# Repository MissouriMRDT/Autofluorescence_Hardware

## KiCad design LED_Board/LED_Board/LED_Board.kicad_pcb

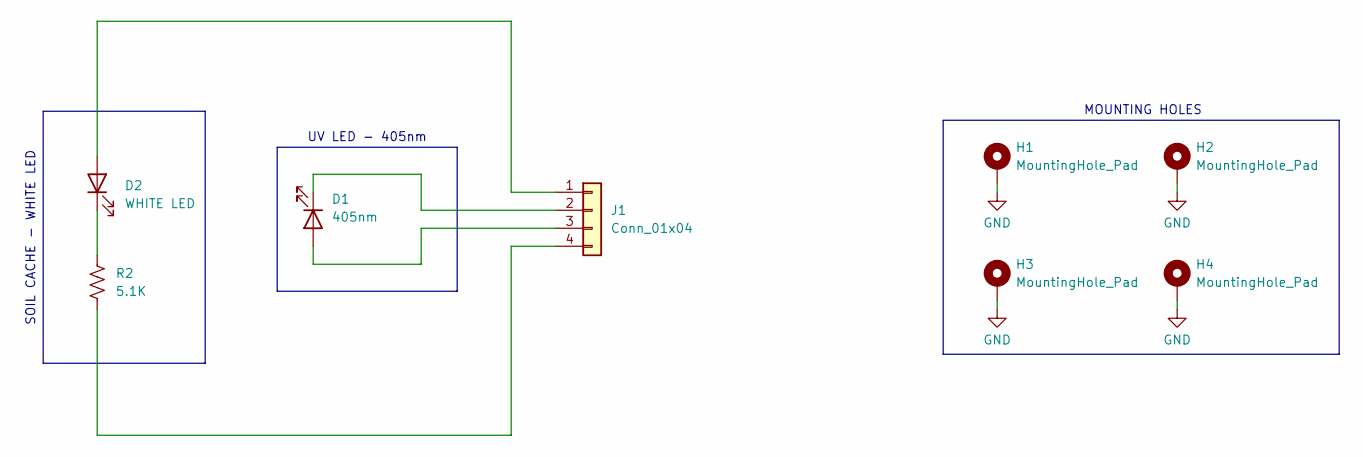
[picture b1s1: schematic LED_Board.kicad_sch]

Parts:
D1: 405nm; CUN06B1B
D2: WHITE LED; D_0603_1608Metric_Pad1.05x0.95mm_HandSolder
H1, H2, H3, H4: MountingHole_Pad; 4_40_Hole_Pad_Via
J1: Conn_01x04; JST_PH_B4B-PH-K_1x04_P2.00mm_Vertical
R2: 5.1K; R_0603_1608Metric_Pad0.98x0.95mm_HandSolder

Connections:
GND: H1.1 (1_1), H2.1 (1_1), H3.1 (1_1), H4.1 (1_1)
unnamed: D2.2 (A), J1.1
unnamed: D2.1 (K), R2.1
unnamed: D1.1, J1.2
unnamed: D1.2, J1.3
unnamed: J1.4, R2.2

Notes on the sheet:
UV LED - 405nm
MOUNTING HOLES
SOIL CACHE - WHITE LED

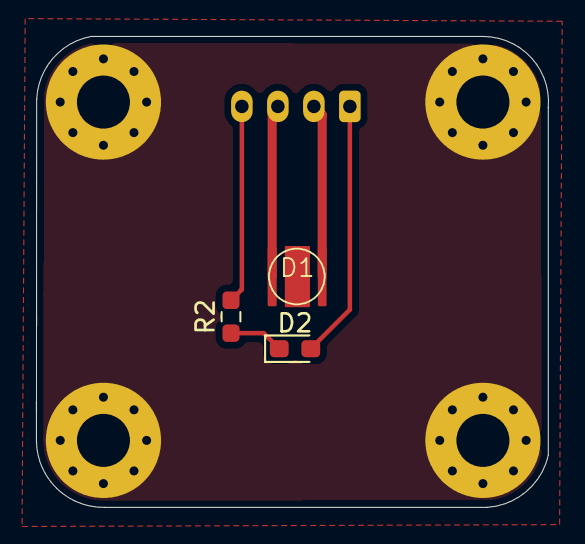
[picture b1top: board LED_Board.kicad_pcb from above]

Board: 2 copper layers, 28.4 x 26.2 mm, 8 parts (1 on the bottom side), 6 nets.

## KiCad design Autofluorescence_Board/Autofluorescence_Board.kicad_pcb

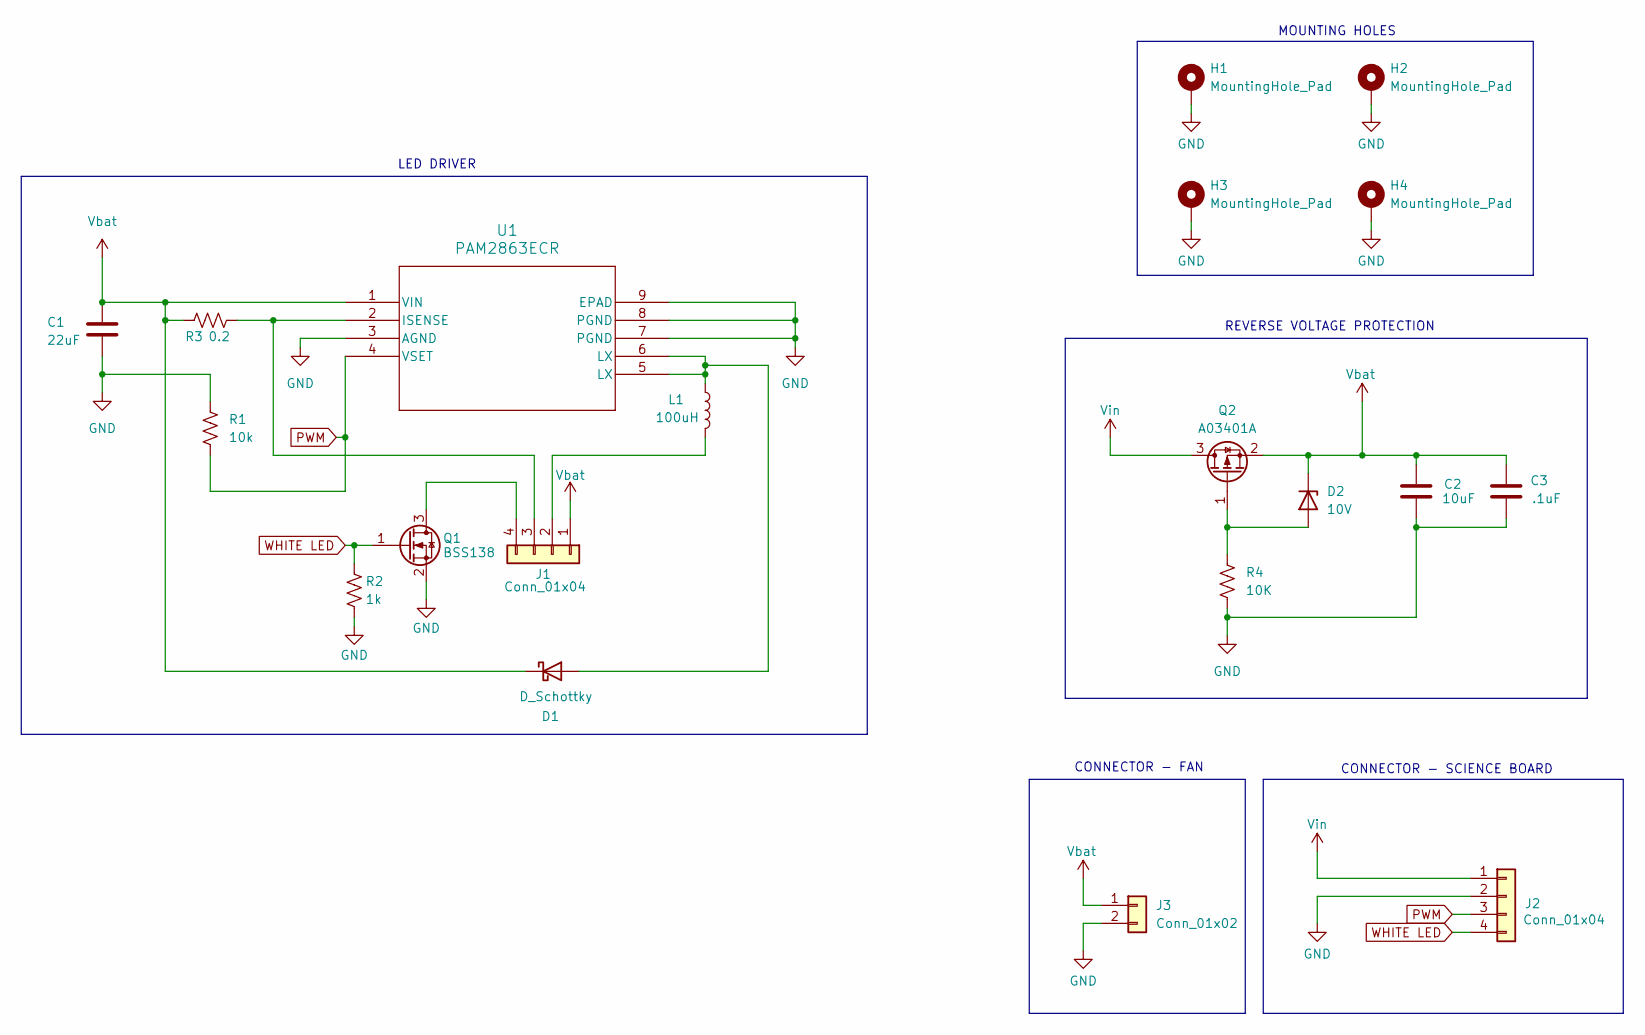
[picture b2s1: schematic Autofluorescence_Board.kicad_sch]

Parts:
C1: 22uF; C_1206_3216Metric_Pad1.33x1.80mm_HandSolder
C2: 10uF; C_0603_1608Metric_Pad1.08x0.95mm_HandSolder
C3: .1uF; C_0603_1608Metric_Pad1.08x0.95mm_HandSolder
D1: D_Schottky; D_SOD-123F
D2: 10V; SOD-123_ONS-L
H1, H2, H3, H4: MountingHole_Pad; 4_40_Hole_Pad_Via
J1, J2: Conn_01x04; JST_PH_S4B-PH-K_1x04_P2.00mm_Horizontal
J3: Conn_01x02; JST_PH_S2B-PH-K_1x02_P2.00mm_Horizontal
L1: 100uH; DR73
Q1: BSS138; SOT-23
Q2: A03401A; SOT-23
R1: 10k; R_0603_1608Metric_Pad0.98x0.95mm_HandSolder
R2: 1k; R_0603_1608Metric_Pad0.98x0.95mm_HandSolder
R3: 0.2; R_0805_2012Metric_Pad1.20x1.40mm_HandSolder
R4: 10K; R_0603_1608Metric_Pad0.98x0.95mm_HandSolder
U1: PAM2863ECR; Diodes_SO-8EP

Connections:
GND: C1.2, C2.2, C3.2, H1.1 (1_1), H2.1 (1_1), H3.1 (1_1), H4.1 (1_1), J2.2, J3.2, Q1.2 (S), R1.2, R2.2, R4.2, U1.3 (AGND), U1.7 (PGND), U1.8 (PGND), U1.9 (EPAD)
unnamed: D1.2 (A), L1.1, U1.5 (LX), U1.6 (LX)
unnamed: D2.2 (A), Q2.1 (G), R4.1
unnamed: J1.2, L1.2
unnamed: J1.3, R3.2, U1.2 (ISENSE)
unnamed: J1.4, Q1.3 (D)
PWM: J2.3, R1.1, U1.4 (VSET)
Vbat: C1.1, C2.1, C3.1, D1.1 (K), D2.1 (K), J1.1, J3.1, Q2.2 (S), R3.1, U1.1 (VIN)
Vin: J2.1, Q2.3 (D)
WHITE LED: J2.4, Q1.1 (G), R2.1

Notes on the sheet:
LED DRIVER
REVERSE VOLTAGE PROTECTION
MOUNTING HOLES
CONNECTOR - SCIENCE BOARD
CONNECTOR - FAN

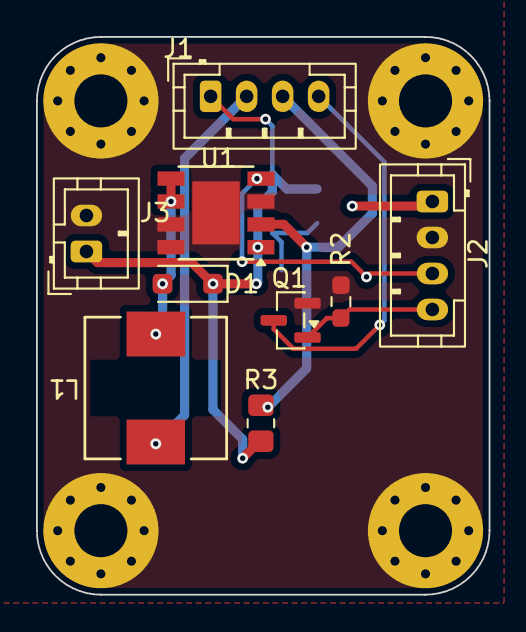
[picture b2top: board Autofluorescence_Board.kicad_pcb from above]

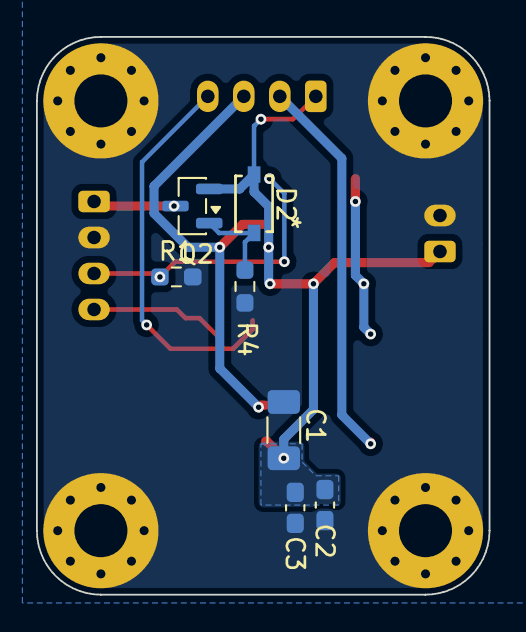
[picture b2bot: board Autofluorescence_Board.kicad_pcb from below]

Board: 2 copper layers, 25.1 x 31.0 mm, 20 parts (7 on the bottom side), 10 nets.

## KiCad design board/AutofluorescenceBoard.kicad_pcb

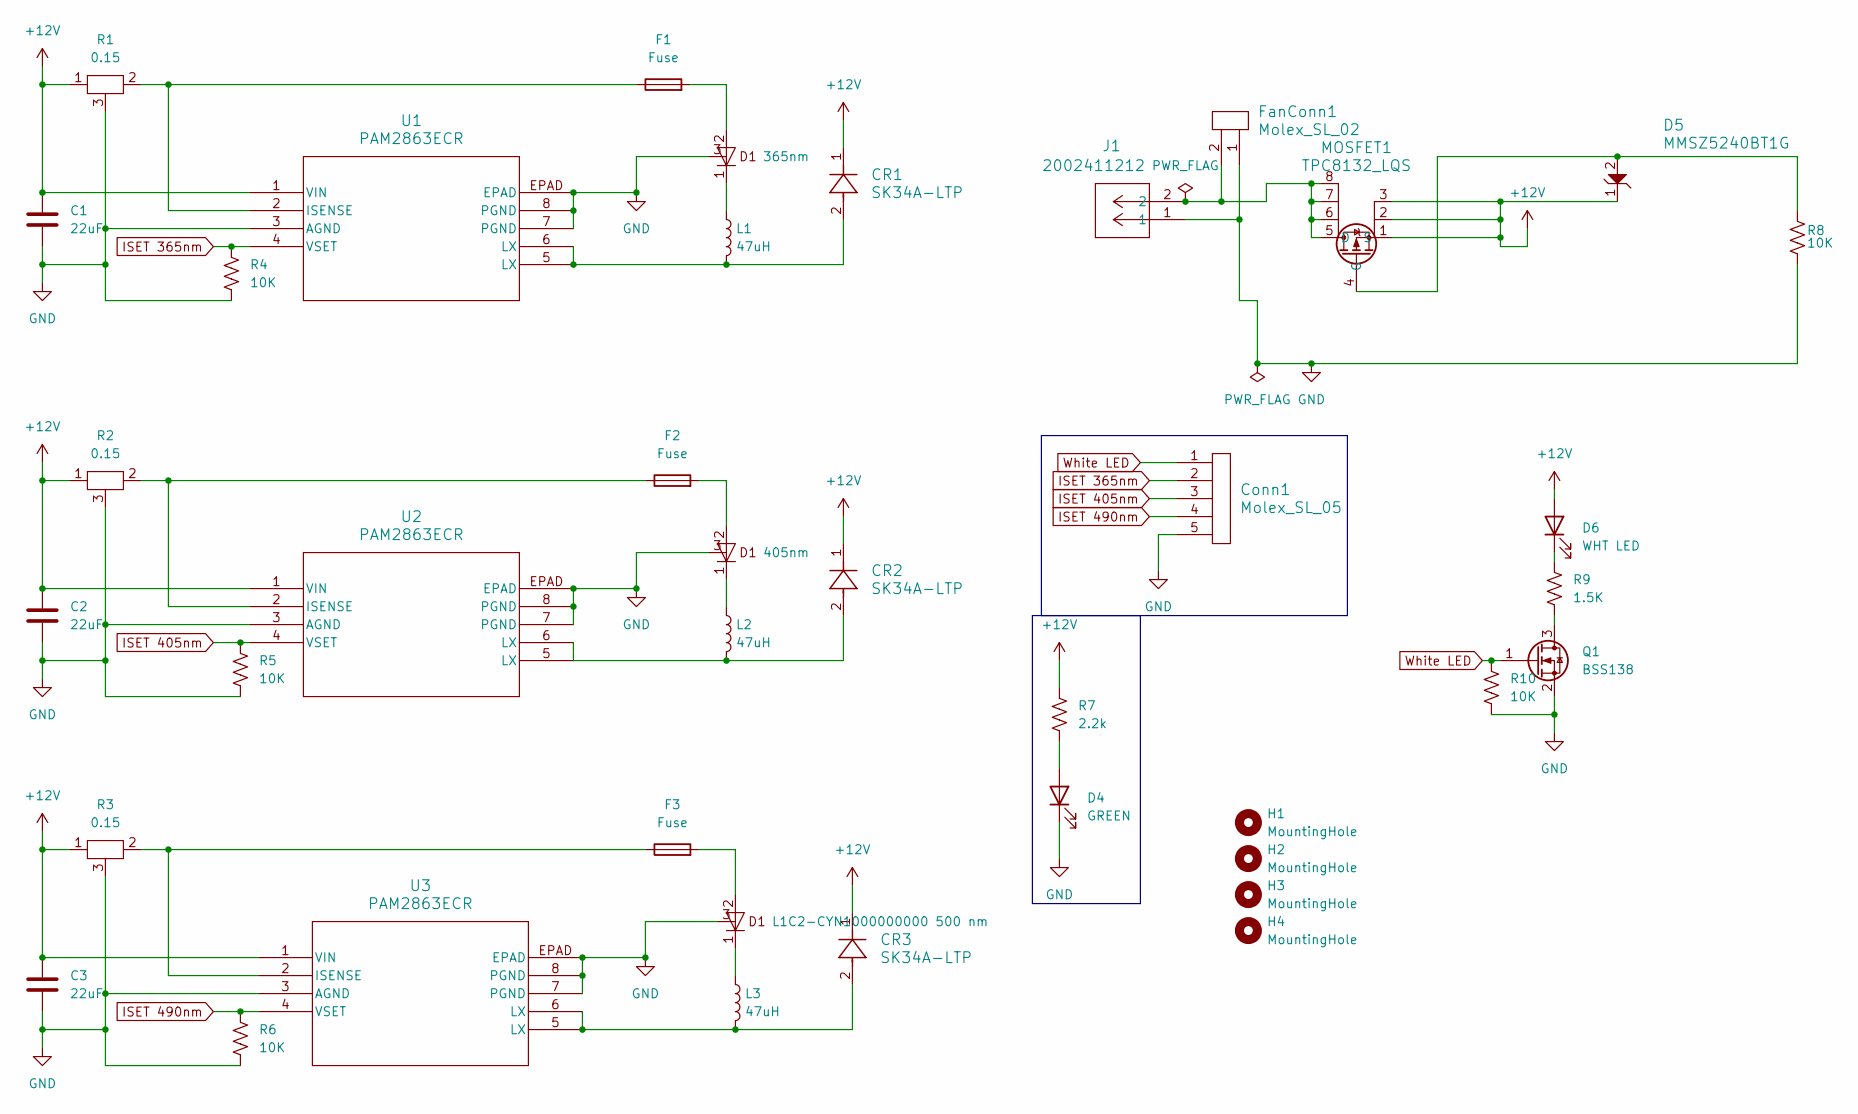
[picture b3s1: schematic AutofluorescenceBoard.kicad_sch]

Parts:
C1, C2, C3: 22uF; C_0805_2012Metric_Pad1.18x1.45mm_HandSolder
CR1, CR2, CR3: SK34A-LTP; SMADO-214AC_MCC
Conn1: Molex_SL_05; MOLEX_SL_05_Horizontal
D1: 365nm
D2: 405nm
D3: L1C2-CYN1000000000 500 nm; 490nm
D4: GREEN; LED_0603_1608Metric_Pad1.05x0.95mm_HandSolder
D5: MMSZ5240BT1G; SOD-123_ONS-L
D6: WHT LED; INS63AT5UW
F1, F2, F3: Fuse; Fuse_0603_1608Metric
FanConn1: Molex_SL_02; MOLEX_SL_02_Horizontal
H1, H2, H3, H4: MountingHole; M2_Hole
J1: 2002411212; MOLEX_SL_02_Horizontal
L1, L2, L3: 47uH; SRN6045TA-470M
MOSFET1: TPC8132_LQS; SOIC-8_3.9x4.9mm_P1.27mm
Q1: BSS138; SOT-23
R1, R2, R3: 0.15; TO508P1229X317-3N
R4, R5, R6, R8, R10: 10K; R_0603_1608Metric_Pad0.98x0.95mm_HandSolder
R7: 2.2k; R_0603_1608Metric_Pad0.98x0.95mm_HandSolder
R9: 1.5K; RES_R0603_ROM-M
U1, U2, U3: PAM2863ECR; SOIC_863ECR_DIO

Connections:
+12V: C1.1, C2.1, C3.1, CR1.1, CR2.1, CR3.1, D5.1, D6.2 (A), MOSFET1.1 (S), MOSFET1.2, MOSFET1.3, R1.1, R2.1, R3.1, R7.1, U1.1 (VIN), U2.1 (VIN), U3.1 (VIN)
GND: C1.2, C2.2, C3.2, Conn1.5, D1.3, D2.3, D3.3, D4.1 (K), FanConn1.1, H1.1, H2.1, H3.1, H4.1, J1.1, Q1.2 (S), R1.3, R2.3, R3.3, R4.2, R5.2, R6.2, R8.1, R10.2, U1.3 (AGND), U1.7 (PGND), U1.8 (PGND), U1.EPAD, U2.3 (AGND), U2.7 (PGND), U2.8 (PGND), U2.EPAD, U3.3 (AGND), U3.7 (PGND), U3.8 (PGND), U3.EPAD
ISET 365nm: Conn1.2, R4.1, U1.4 (VSET)
ISET 405nm: Conn1.3, R5.1, U2.4 (VSET)
ISET 490nm: Conn1.4, R6.1, U3.4 (VSET)
unnamed: CR1.2, L1.2, U1.5 (LX), U1.6 (LX)
unnamed: CR2.2, L2.2, U2.5 (LX), U2.6 (LX)
unnamed: CR3.2, L3.2, U3.5 (LX), U3.6 (LX)
unnamed: D1.1, L1.1
unnamed: D1.2, F1.2
unnamed: D2.1, L2.1
unnamed: D2.2, F2.2
unnamed: D3.1, L3.1
unnamed: D3.2, F3.2
unnamed: D4.2 (A), R7.2
unnamed: D6.1 (K), R9.1
unnamed: FanConn1.2, J1.2, MOSFET1.5 (D), MOSFET1.6, MOSFET1.7, MOSFET1.8
unnamed: D5.2, MOSFET1.4 (G), R8.2
unnamed: Q1.3 (D), R9.2
unnamed: F1.1, R1.2, U1.2 (ISENSE)
unnamed: F2.1, R2.2, U2.2 (ISENSE)
unnamed: F3.1, R3.2, U3.2 (ISENSE)
White LED: Conn1.1, Q1.1 (G), R10.1

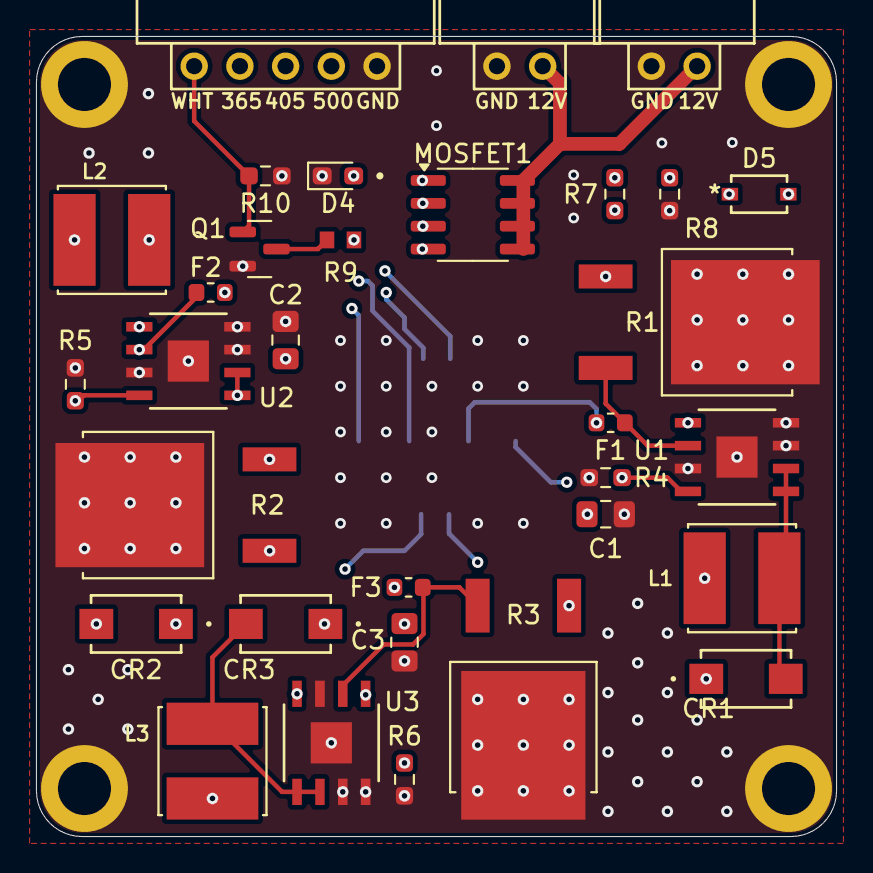
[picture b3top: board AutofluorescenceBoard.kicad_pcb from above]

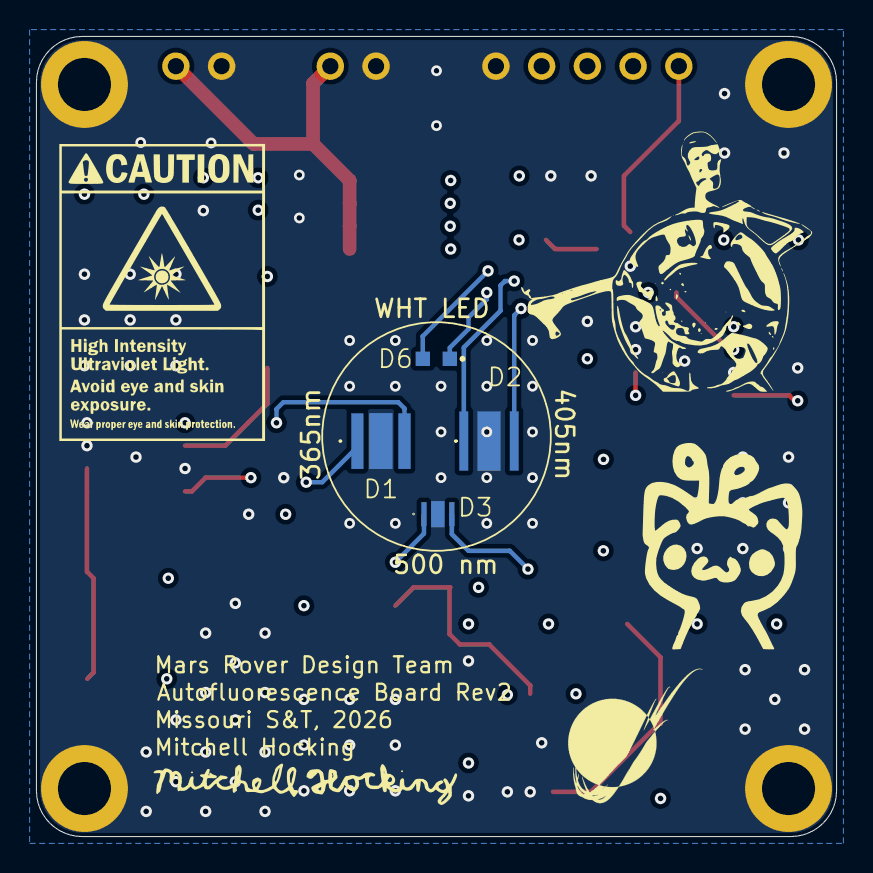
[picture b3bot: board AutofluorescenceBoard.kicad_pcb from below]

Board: 4 copper layers, 44.4 x 44.5 mm, 40 parts (4 on the bottom side), 23 nets.

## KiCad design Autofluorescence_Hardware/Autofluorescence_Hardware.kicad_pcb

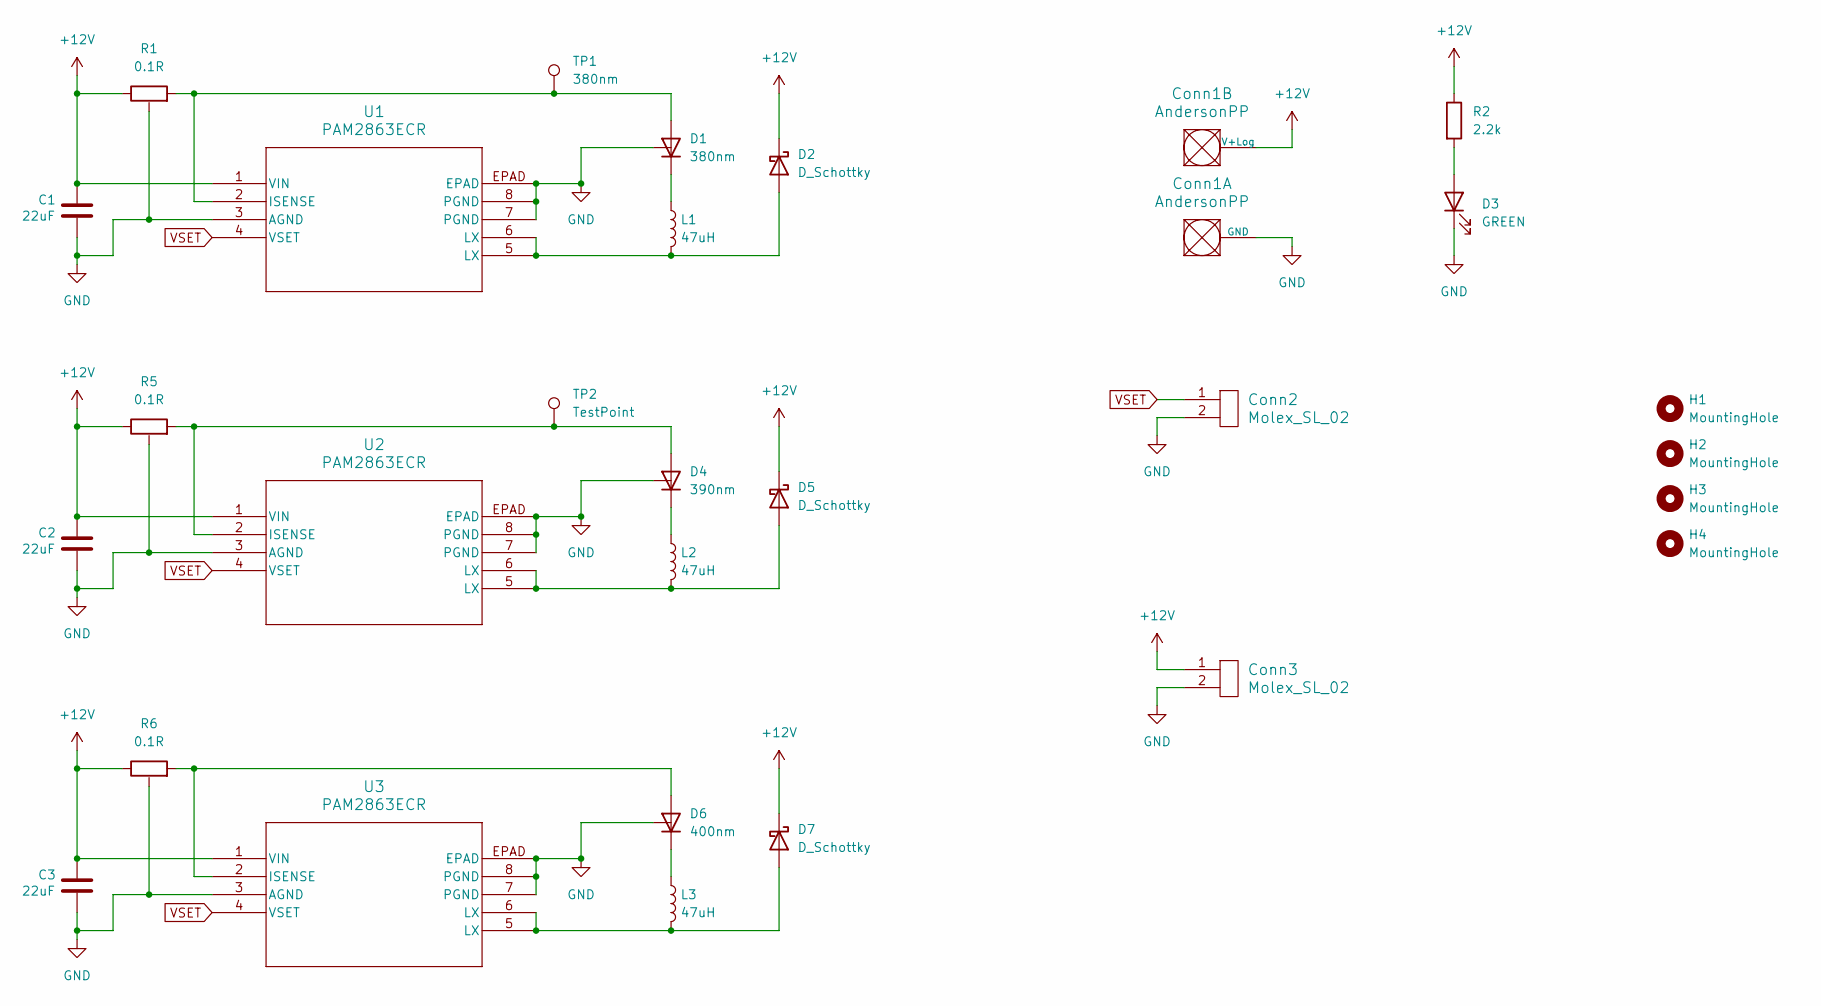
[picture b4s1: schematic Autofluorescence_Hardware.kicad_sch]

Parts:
C1, C2, C3: 22uF; C_0805_2012Metric_Pad1.18x1.45mm_HandSolder
Conn1: AndersonPP; Square_Anderson_2_H_Side_By_Side
Conn2, Conn3: Molex_SL_02; MOLEX_SL_02_Horizontal
D1: 380nm; SBT-10X-UV-A120-AHXXX-22
D2, D5, D7: D_Schottky; SK34A-LTP
D3: GREEN; LED_0603_1608Metric_Pad1.05x0.95mm_HandSolder
D4: 390nm; SBT-10X-UV-A120-AHXXX-22
D6: 400nm; SBT-10X-UV-A120-AHXXX-22
H1, H2, H3, H4: MountingHole; MountingHole_3.5mm
L1, L2, L3: 47uH; SRN6045TA-470M
R1, R5, R6: 0.1R; PWR163S-25-R100FE
R2: 2.2k; R_0603_1608Metric_Pad0.98x0.95mm_HandSolder
TP1: 380nm; TestPoint_Pad_D1.5mm
TP2: TestPoint; TestPoint_Pad_D1.5mm
U1, U2, U3: PAM2863ECR; SOIC_863ECR_DIO

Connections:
+12V: C1.1, C2.1, C3.1, Conn1.2 (V+Log), Conn3.1, D2.1 (K), D5.1 (K), D7.1 (K), R1.1, R2.1, R5.1, R6.1, U1.1 (VIN), U2.1 (VIN), U3.1 (VIN)
GND: C1.2, C2.2, C3.2, Conn1.1 (GND), Conn2.2, Conn3.2, D1.3, D3.1 (K), D4.3, D6.3, R1.3, R5.3, R6.3, U1.3 (AGND), U1.7 (PGND), U1.8 (PGND), U1.EPAD, U2.3 (AGND), U2.7 (PGND), U2.8 (PGND), U2.EPAD, U3.3 (AGND), U3.7 (PGND), U3.8 (PGND), U3.EPAD
unnamed: D1.2 (A), R1.2, TP1.1, U1.2 (ISENSE)
unnamed: D1.1 (K), L1.1
unnamed: D2.2 (A), L1.2, U1.5 (LX), U1.6 (LX)
unnamed: D3.2 (A), R2.2
unnamed: D4.2 (A), R5.2, TP2.1, U2.2 (ISENSE)
unnamed: D4.1 (K), L2.1
unnamed: D5.2 (A), L2.2, U2.5 (LX), U2.6 (LX)
unnamed: D6.2 (A), R6.2, U3.2 (ISENSE)
unnamed: D6.1 (K), L3.1
unnamed: D7.2 (A), L3.2, U3.5 (LX), U3.6 (LX)
VSET: Conn2.1, U1.4 (VSET), U2.4 (VSET), U3.4 (VSET)

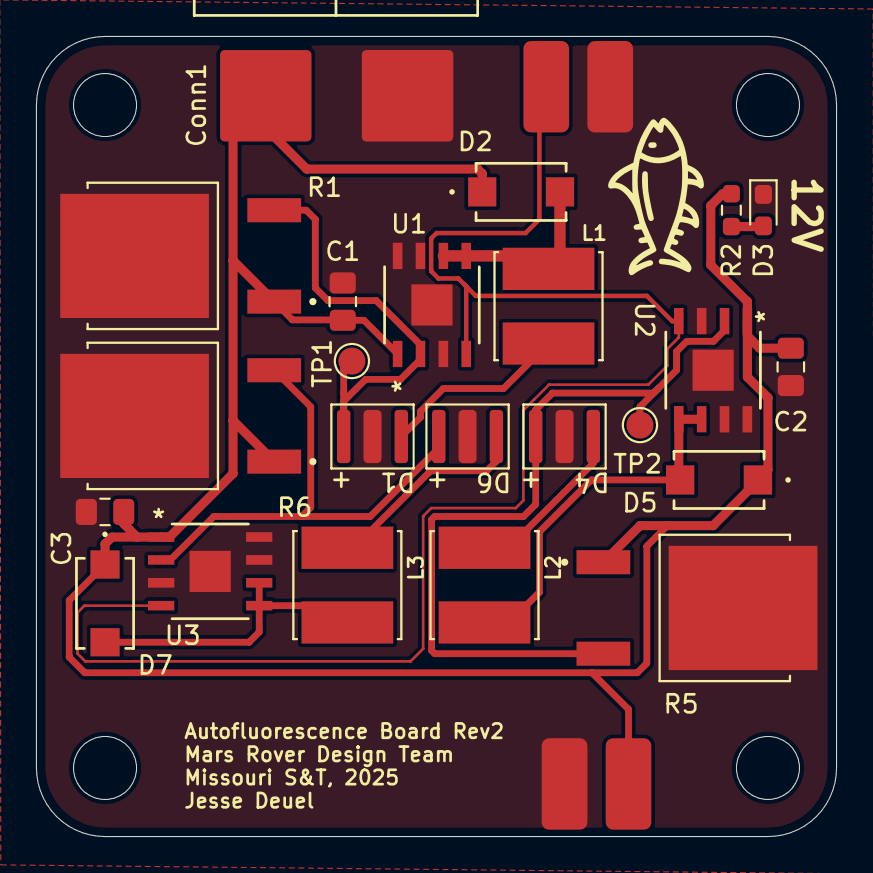
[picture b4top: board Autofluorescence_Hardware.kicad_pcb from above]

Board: 2 copper layers, 44.4 x 44.5 mm, 29 parts (0 on the bottom side), 13 nets.

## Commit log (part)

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2024-10-03 Initial repository
2024-12-17 Finished layout and started schematic
2024-12-18 Finished layout
2025-02-10 Fixed for aluminum core pcb
2025-09-12 Added workflow
2025-10-08 Added PAM2863ECR Symbol
2025-10-09 First Draft of LED Drivers
2025-10-09 Edited Components
2025-10-23 Added Some Footprints
2025-10-24 Changed Led 365
2025-10-30 Added Rev.1 Mods, Datasheets and Footprints
2025-10-30 Added 490nm Fuse Datasheet
2025-10-31 Added LED Footprints and started Layout
2025-10-31 Layout Start
2025-11-01 Layout
2025-11-02 Random Footprint changes
2025-11-02 Footprints
    -Added custom footprints
    -added more datasheet links
2025-11-02 Started layout
2025-11-02 First Draft of Layout done
    -Traces are proofs of concept. NEED TO BE COMPLETELY REDONE. No current calculation was done and the ground plane is mad T_T
    -Board also needs to be actually the size said in CDR presentation. Just didn't want to spend the time perfectly sizing to the value I wanted.
2025-11-12 Layout Ground Fixes
2025-11-12 Added White LED
2025-11-12 Changed Resistors and Board/Mounting Hole Dimensions
2025-11-14 Silkscreens :)
2025-11-15 Layout Changes from CDR
2025-11-15 Fixed Connection Issues
    MOSFET was messed up, fixed grounding things, and made all traces at least 10 mils.
2025-11-16 Confined leds white and UV to .25 in radius
2025-11-17 Add Mitchell's signature
2025-11-17 Added Silkscreen drawing
2025-11-18 Added back the wilted rose silkscreen
2025-11-18 Finished up
    adjust mounting holes and light sealable space
    no 90 degrees
    Trace width 12 V 5A
    Add silkscreen documentation
2026-02-27 Start of Rev2
    I'll be honest, I have no idea what I'm pushing. I can't view the changes and i need to push for the start of Rev2
2026-02-27 Wizard
2026-02-27 Rev2 Initial Component Placement
2026-02-27 Fixed Errror
2026-02-27 Fixed Footprint for Zener Diode
2026-03-02 Added some traces and update some footprints
2026-03-03 Added Planes
2026-03-03 Layout?
2026-03-16 Fixed Layout
2026-03-16 Some Board Review Changes
2026-03-16 Screwed Up MRDT Library on Laptop
2026-03-16 Updated Schematic, Mounting Holes, and a couple 3D models
2026-03-16 Fixed white led silkscreen
2026-03-16 Added 3D models and some silkscreen
2026-03-17 Added GND Thermal stuff on power plane
2026-03-17 Added Signature
2026-03-18 VIAS
2026-03-18 Added Diode Direction Marker for D4
2026-03-18 Silkscreens
2026-03-20 Fixed Via Stitching, they werent ground for some reason
2026-03-23 Final design files as ordered
